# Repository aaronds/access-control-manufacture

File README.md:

# Access Control Manufacture

CAD / CAM assets for manufacturing access control boxes (aka "bleepy boxes").

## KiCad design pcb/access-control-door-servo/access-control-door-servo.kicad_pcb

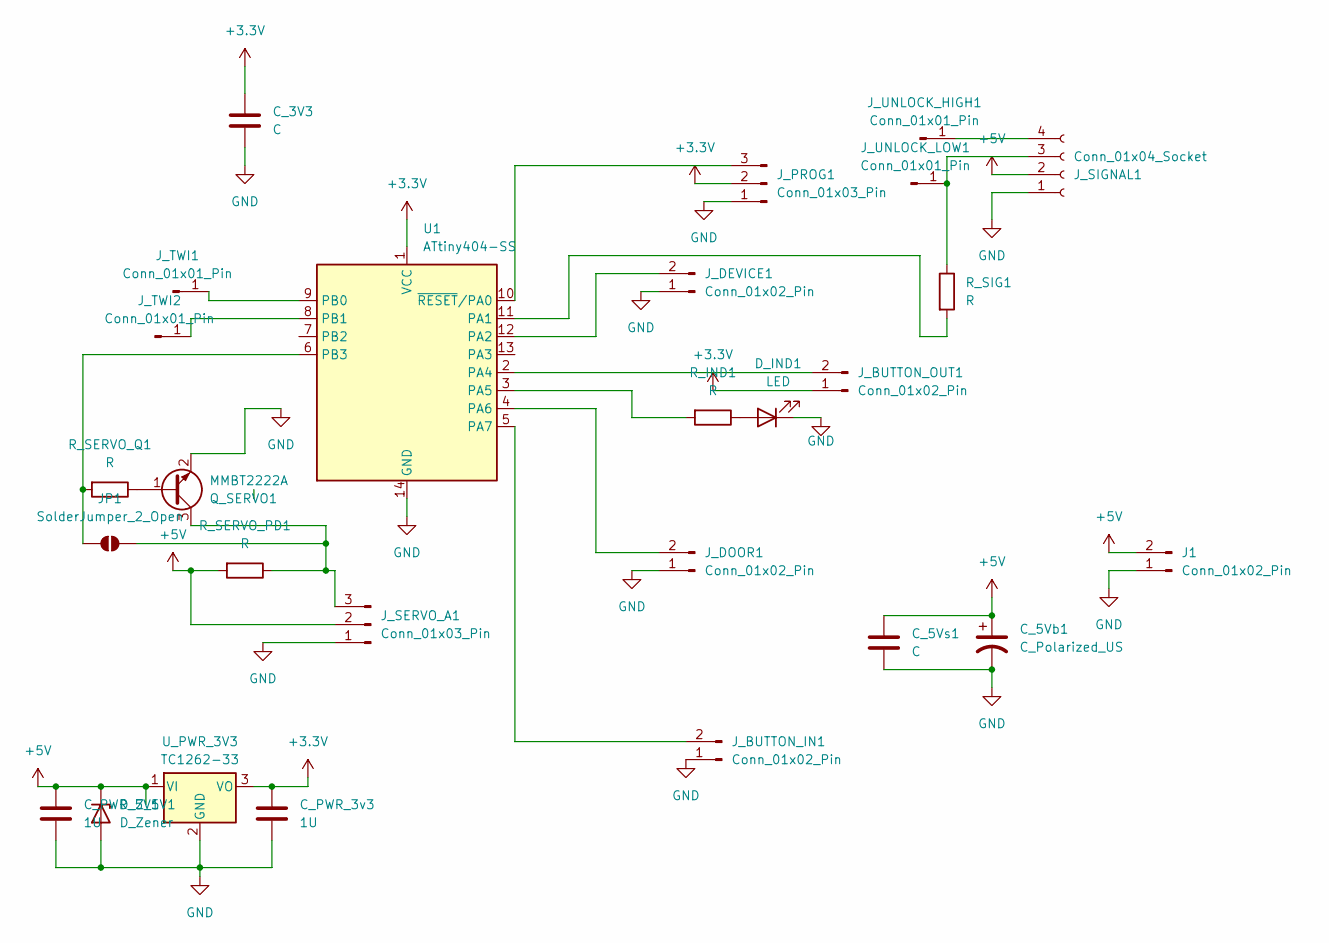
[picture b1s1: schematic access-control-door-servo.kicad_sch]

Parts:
C_3V3, C_5Vs1: C; C_1206_3216Metric
C_5Vb1: C_Polarized_US; CP_Radial_D5.0mm_P2.50mm
C_PWR_3v3, C_PWR_5V1: 1U; C_1206_3216Metric_Pad1.33x1.80mm_HandSolder
D_IND1: LED; LED_D10.0mm
D_Z_5V1: D_Zener; D_1206_3216Metric_Pad1.42x1.75mm_HandSolder
J1: Conn_01x02_Pin; JST_XH_B2B-XH-A_1x02_P2.50mm_Vertical
JP1: SolderJumper_2_Open; SolderJumper-2_P1.3mm_Open_TrianglePad1.0x1.5mm
J_BUTTON_IN1: Conn_01x02_Pin; PinSocket_1x02_P2.54mm_Vertical
J_BUTTON_OUT1: Conn_01x02_Pin; PinSocket_1x02_P2.54mm_Vertical
J_DEVICE1: Conn_01x02_Pin; PinHeader_1x02_P2.54mm_Vertical
J_DOOR1: Conn_01x02_Pin; PinHeader_1x02_P2.54mm_Vertical
J_PROG1: Conn_01x03_Pin; PinHeader_1x03_P2.54mm_Vertical
J_SERVO_A1: Conn_01x03_Pin; PinHeader_1x03_P2.54mm_Vertical
J_SIGNAL1: Conn_01x04_Socket; JST_XH_B4B-XH-A_1x04_P2.50mm_Vertical
J_TWI1, J_TWI2: Conn_01x01_Pin; SolderWirePad_1x01_SMD_1x2mm
J_UNLOCK_HIGH1: Conn_01x01_Pin; SolderWirePad_1x01_SMD_1x2mm
J_UNLOCK_LOW1: Conn_01x01_Pin; SolderWirePad_1x01_SMD_1x2mm
Q_SERVO1: MMBT2222A; SOT-23W_Handsoldering
R_IND1: R; R_1206_3216Metric
R_SERVO_PD1: R; R_1206_3216Metric
R_SERVO_Q1: R; R_1206_3216Metric
R_SIG1: R; R_1206_3216Metric
U1: ATtiny404-SS; SOIC-14_3.9x8.7mm_P1.27mm
U_PWR_3V3: TC1262-33; SOT-223-3_TabPin2

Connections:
+3.3V: C_3V3.1, C_PWR_3v3.1, J_BUTTON_OUT1.1, J_PROG1.2, U1.1 (VCC), U_PWR_3V3.3 (VO)
+5V: C_5Vb1.1, C_5Vs1.1, C_PWR_5V1.1, D_Z_5V1.1 (K), J1.2, J_SERVO_A1.2, J_SIGNAL1.2, R_SERVO_PD1.2, U_PWR_3V3.1 (VI)
GND: C_3V3.2, C_5Vb1.2, C_5Vs1.2, C_PWR_3v3.2, C_PWR_5V1.2, D_IND1.1 (K), D_Z_5V1.2 (A), J1.1, J_BUTTON_IN1.1, J_DEVICE1.1, J_DOOR1.1, J_PROG1.1, J_SERVO_A1.1, J_SIGNAL1.1, Q_SERVO1.2 (E), U1.14 (GND), U_PWR_3V3.2 (GND)
unnamed: D_IND1.2 (A), R_IND1.1
unnamed: JP1.1 (A), R_SERVO_Q1.2, U1.6 (PB3)
unnamed: JP1.2 (B), J_SERVO_A1.3, Q_SERVO1.3 (C), R_SERVO_PD1.1
unnamed: J_BUTTON_IN1.2, U1.5 (PA7)
unnamed: J_BUTTON_OUT1.2, U1.2 (PA4)
unnamed: J_DEVICE1.2, U1.12 (PA2)
unnamed: J_DOOR1.2, U1.4 (PA6)
unnamed: J_PROG1.3, U1.10 (~RESET/PA0)
unnamed: J_SIGNAL1.3, J_UNLOCK_LOW1.1, R_SIG1.1
unnamed: J_SIGNAL1.4, J_UNLOCK_HIGH1.1
unnamed: J_TWI1.1, U1.9 (PB0)
unnamed: J_TWI2.1, U1.8 (PB1)
unnamed: Q_SERVO1.1 (B), R_SERVO_Q1.1
unnamed: R_SIG1.2, U1.11 (PA1)
unnamed: R_IND1.2, U1.3 (PA5)

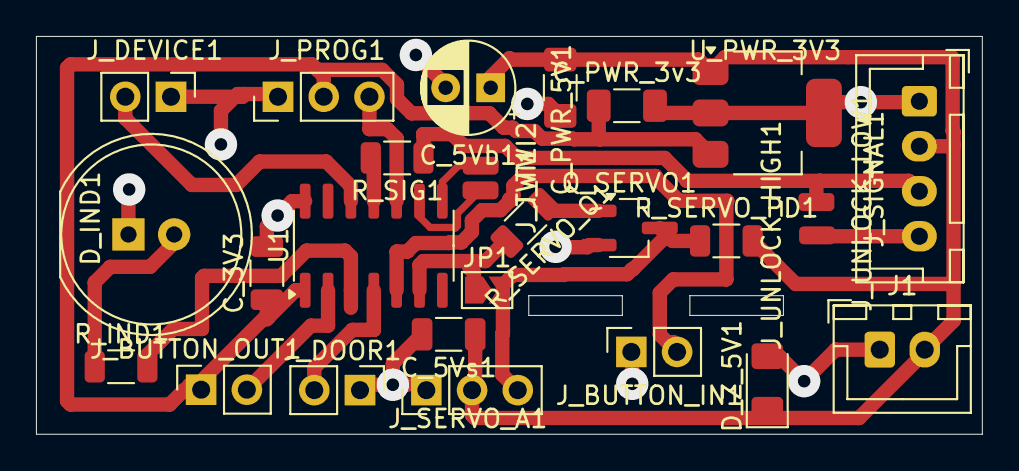
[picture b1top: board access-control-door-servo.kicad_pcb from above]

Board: 2 copper layers, 52.5 x 22.1 mm, 27 parts (0 on the bottom side), 18 nets.

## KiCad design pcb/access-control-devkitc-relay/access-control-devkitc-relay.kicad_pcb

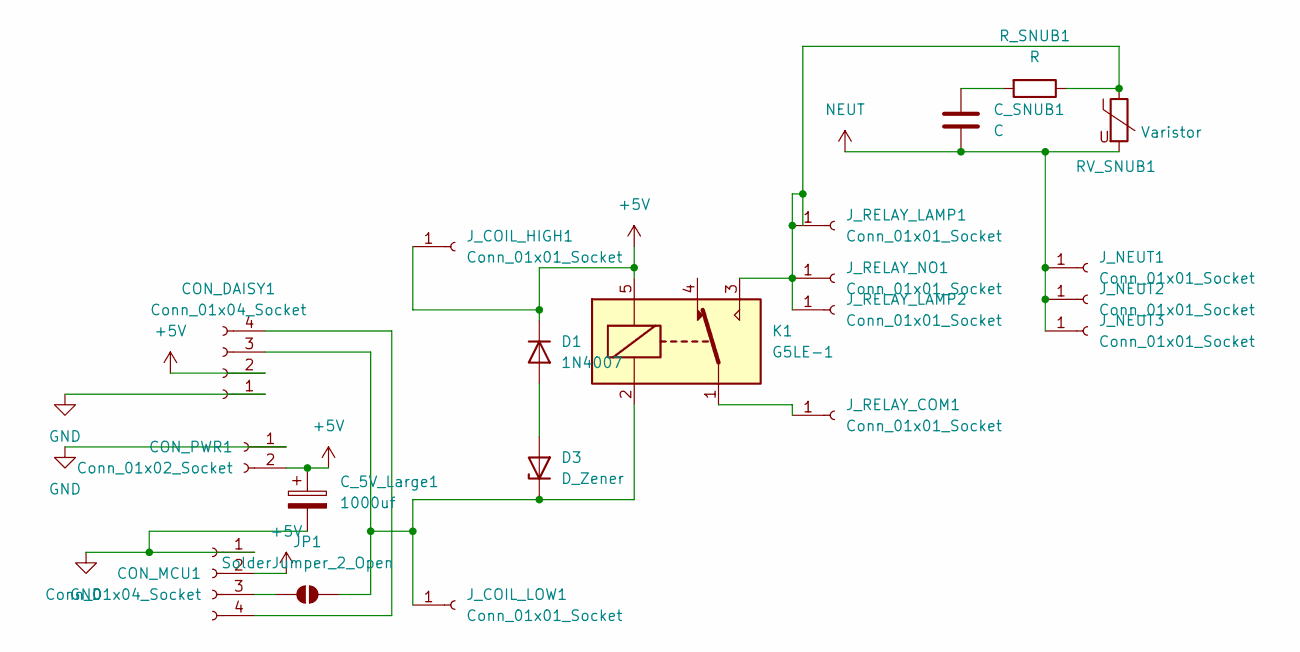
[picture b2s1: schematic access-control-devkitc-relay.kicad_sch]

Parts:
CON_DAISY1: Conn_01x04_Socket; JST_XA_B04B-XASK-1_1x04_P2.50mm_Vertical
CON_MCU1: Conn_01x04_Socket; PinHeader_1x04_P2.54mm_Vertical
CON_PWR1: Conn_01x02_Socket; JST_XH_B2B-XH-A_1x02_P2.50mm_Vertical
C_5V_Large1: 1000uf; CP_Radial_D8.0mm_P5.00mm
C_SNUB1: C; CP_Axial_L10.0mm_D6.0mm_P15.00mm_Horizontal
D1: 1N4007; D_DO-41_SOD81_P10.16mm_Horizontal
D3: D_Zener; D_DO-41_SOD81_P10.16mm_Horizontal
JP1: SolderJumper_2_Open; SolderJumper-2_P1.3mm_Open_TrianglePad1.0x1.5mm
J_COIL_HIGH1: Conn_01x01_Socket; SolderWire-1sqmm_1x01_D1.4mm_OD2.7mm
J_COIL_LOW1: Conn_01x01_Socket; SolderWire-1sqmm_1x01_D1.4mm_OD2.7mm
J_NEUT1, J_NEUT2, J_NEUT3: Conn_01x01_Socket; SolderWire-2.5sqmm_1x01_D2.4mm_OD4.4mm
J_RELAY_COM1: Conn_01x01_Socket; SolderWire-2.5sqmm_1x01_D2.4mm_OD4.4mm
J_RELAY_LAMP1, J_RELAY_LAMP2: Conn_01x01_Socket; SolderWire-2.5sqmm_1x01_D2.4mm_OD4.4mm
J_RELAY_NO1: Conn_01x01_Socket; SolderWire-2.5sqmm_1x01_D2.4mm_OD4.4mm
K1: G5LE-1; Relay_SPDT_Omron-G5LE-1
RV_SNUB1: Varistor; RV_Disc_D12mm_W3.9mm_P7.5mm
R_SNUB1: R; R_Axial_DIN0617_L17.0mm_D6.0mm_P20.32mm_Horizontal

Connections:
+5V: CON_DAISY1.2, CON_MCU1.2, CON_PWR1.2, C_5V_Large1.1, D1.1 (K), J_COIL_HIGH1.1, K1.5
GND: CON_DAISY1.1, CON_MCU1.1, CON_PWR1.1, C_5V_Large1.2
NEUT: C_SNUB1.2, J_NEUT1.1, J_NEUT2.1, J_NEUT3.1, RV_SNUB1.2
unnamed: CON_DAISY1.3, D3.1 (K), JP1.2 (B), J_COIL_LOW1.1, K1.2
unnamed: CON_DAISY1.4, CON_MCU1.4
unnamed: CON_MCU1.3, JP1.1 (A)
unnamed: C_SNUB1.1, R_SNUB1.2
unnamed: D1.2 (A), D3.2 (A)
unnamed: J_RELAY_COM1.1, K1.1
unnamed: J_RELAY_LAMP1.1, J_RELAY_LAMP2.1, J_RELAY_NO1.1, K1.3, RV_SNUB1.1, R_SNUB1.1

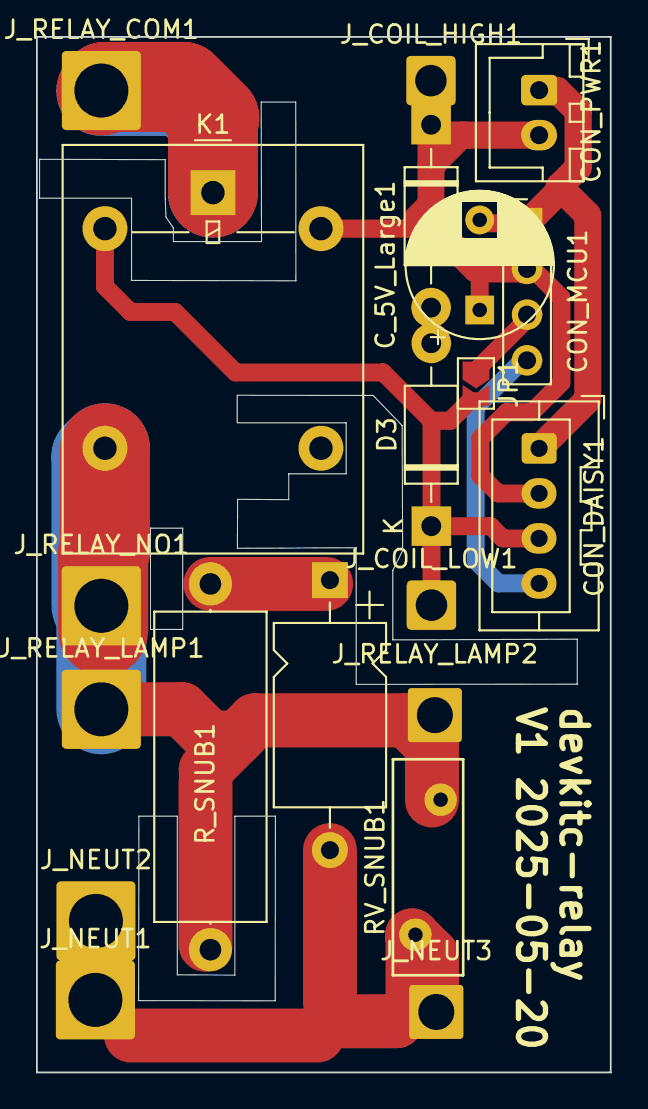
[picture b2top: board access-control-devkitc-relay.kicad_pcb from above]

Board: 2 copper layers, 31.9 x 57.5 mm, 20 parts (0 on the bottom side), 10 nets.

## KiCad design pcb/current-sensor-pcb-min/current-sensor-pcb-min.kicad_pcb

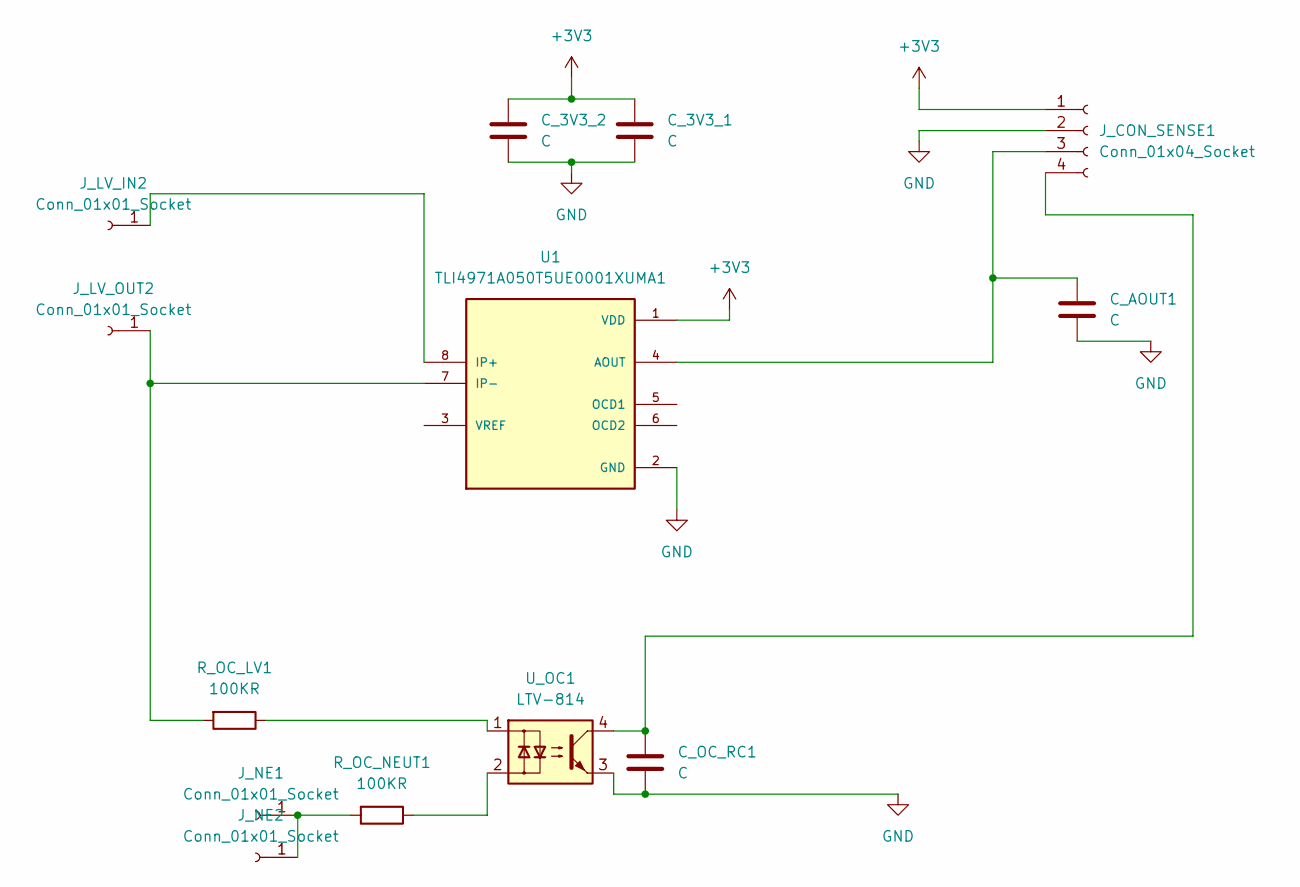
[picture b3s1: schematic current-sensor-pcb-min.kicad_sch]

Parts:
C_3V3_1, C_3V3_2: C; C_Disc_D3.8mm_W2.6mm_P2.50mm
C_AOUT1: C; C_Disc_D3.8mm_W2.6mm_P2.50mm
C_OC_RC1: C; C_Disc_D5.0mm_W2.5mm_P5.00mm
J_CON_SENSE1: Conn_01x04_Socket; PinHeader_1x04_P2.54mm_Vertical
J_LV_IN2: Conn_01x01_Socket; SolderWirePad_1x01_SMD_5x10mm
J_LV_OUT2: Conn_01x01_Socket; SolderWirePad_1x01_SMD_5x10mm
J_NE1, J_NE2: Conn_01x01_Socket; SolderWire-2.5sqmm_1x01_D2.4mm_OD3.6mm
R_OC_LV1: 100KR; R_Axial_DIN0617_L17.0mm_D6.0mm_P20.32mm_Horizontal
R_OC_NEUT1: 100KR; R_Axial_DIN0617_L17.0mm_D6.0mm_P20.32mm_Horizontal
U1: TLI4971A050T5UE0001XUMA1; IC_TLI4971A050T5UE0001XUMA1; PARTREV 1.20
U_OC1: LTV-814; DIP-4_W7.62mm

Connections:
+3V3: C_3V3_1.1, C_3V3_2.1, J_CON_SENSE1.1, U1.1 (VDD)
GND: C_3V3_1.2, C_3V3_2.2, C_AOUT1.2, C_OC_RC1.2, J_CON_SENSE1.2, U1.2 (GND), U_OC1.3
unnamed: C_AOUT1.1, J_CON_SENSE1.3, U1.4 (AOUT)
unnamed: C_OC_RC1.1, J_CON_SENSE1.4, U_OC1.4
unnamed: J_LV_IN2.1, U1.8 (IP+)
unnamed: J_LV_OUT2.1, R_OC_LV1.2, U1.7 (IP-)
unnamed: J_NE1.1, J_NE2.1, R_OC_NEUT1.2
unnamed: R_OC_LV1.1, U_OC1.1
unnamed: R_OC_NEUT1.1, U_OC1.2

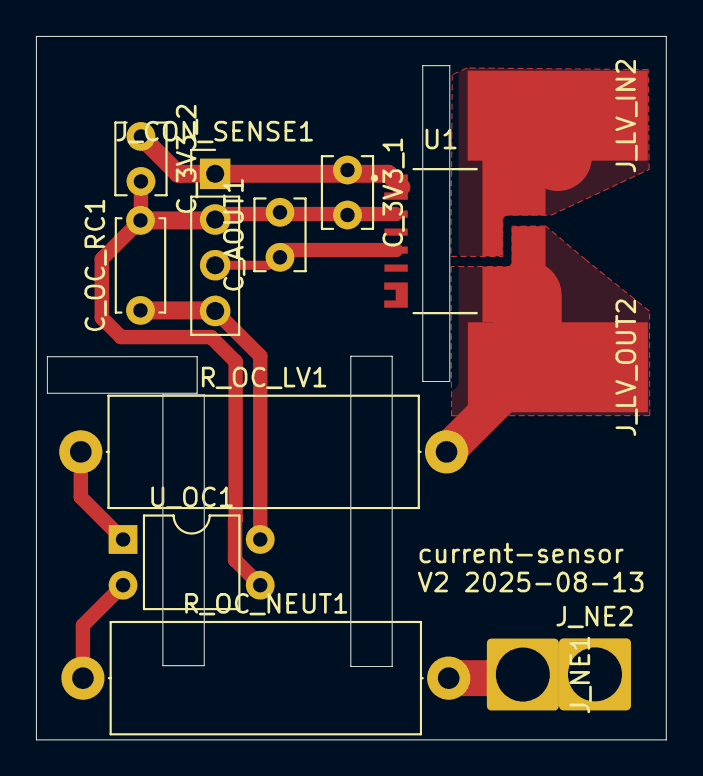
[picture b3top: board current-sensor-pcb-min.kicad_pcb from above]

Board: 2 copper layers, 35.0 x 39.1 mm, 13 parts (0 on the bottom side), 9 nets.

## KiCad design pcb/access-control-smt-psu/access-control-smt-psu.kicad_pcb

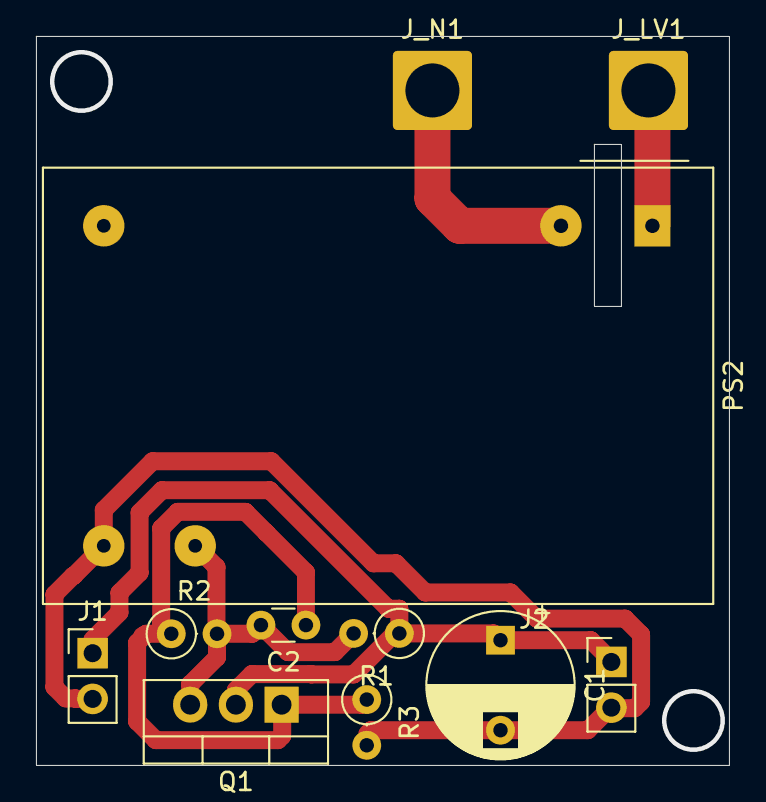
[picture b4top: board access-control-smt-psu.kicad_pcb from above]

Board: 2 copper layers, 38.5 x 40.5 mm, 11 parts (0 on the bottom side), 5 nets.

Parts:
C1: C_Polarized; CP_Radial_D8.0mm_P5.00mm
C2: C1u; C_Disc_D3.0mm_W1.6mm_P2.50mm
J1, J2: Conn_01x02_Socket; PinHeader_1x02_P2.54mm_Vertical
J_LV1: Conn_01x01_Pin; SolderWire-2.5sqmm_1x01_D2.4mm_OD4.4mm
J_N1: Conn_01x01_Pin; SolderWire-2.5sqmm_1x01_D2.4mm_OD4.4mm
PS2: IRM-03-5; Converter_ACDC_MeanWell_IRM-03-xx_THT
Q1: IRF9540N; TO-220-3_Vertical
R1: R1; R_Axial_DIN0207_L6.3mm_D2.5mm_P2.54mm_Vertical
R2: R150k; R_Axial_DIN0207_L6.3mm_D2.5mm_P2.54mm_Vertical
R3: R8.6k; R_Axial_DIN0207_L6.3mm_D2.5mm_P2.54mm_Vertical

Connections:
unnamed: C1.1, J1.1, J2.1, Q1.2 (D), R1.1
unnamed: J_LV1.1, PS2.1 (AC/L)
unnamed: J_N1.1, PS2.3 (AC/N)
unnamed: C2.2, PS2.16 (+Vo), Q1.3 (S), R1.2, R2.2
unnamed: C2.1, Q1.1 (G), R2.1, R3.1

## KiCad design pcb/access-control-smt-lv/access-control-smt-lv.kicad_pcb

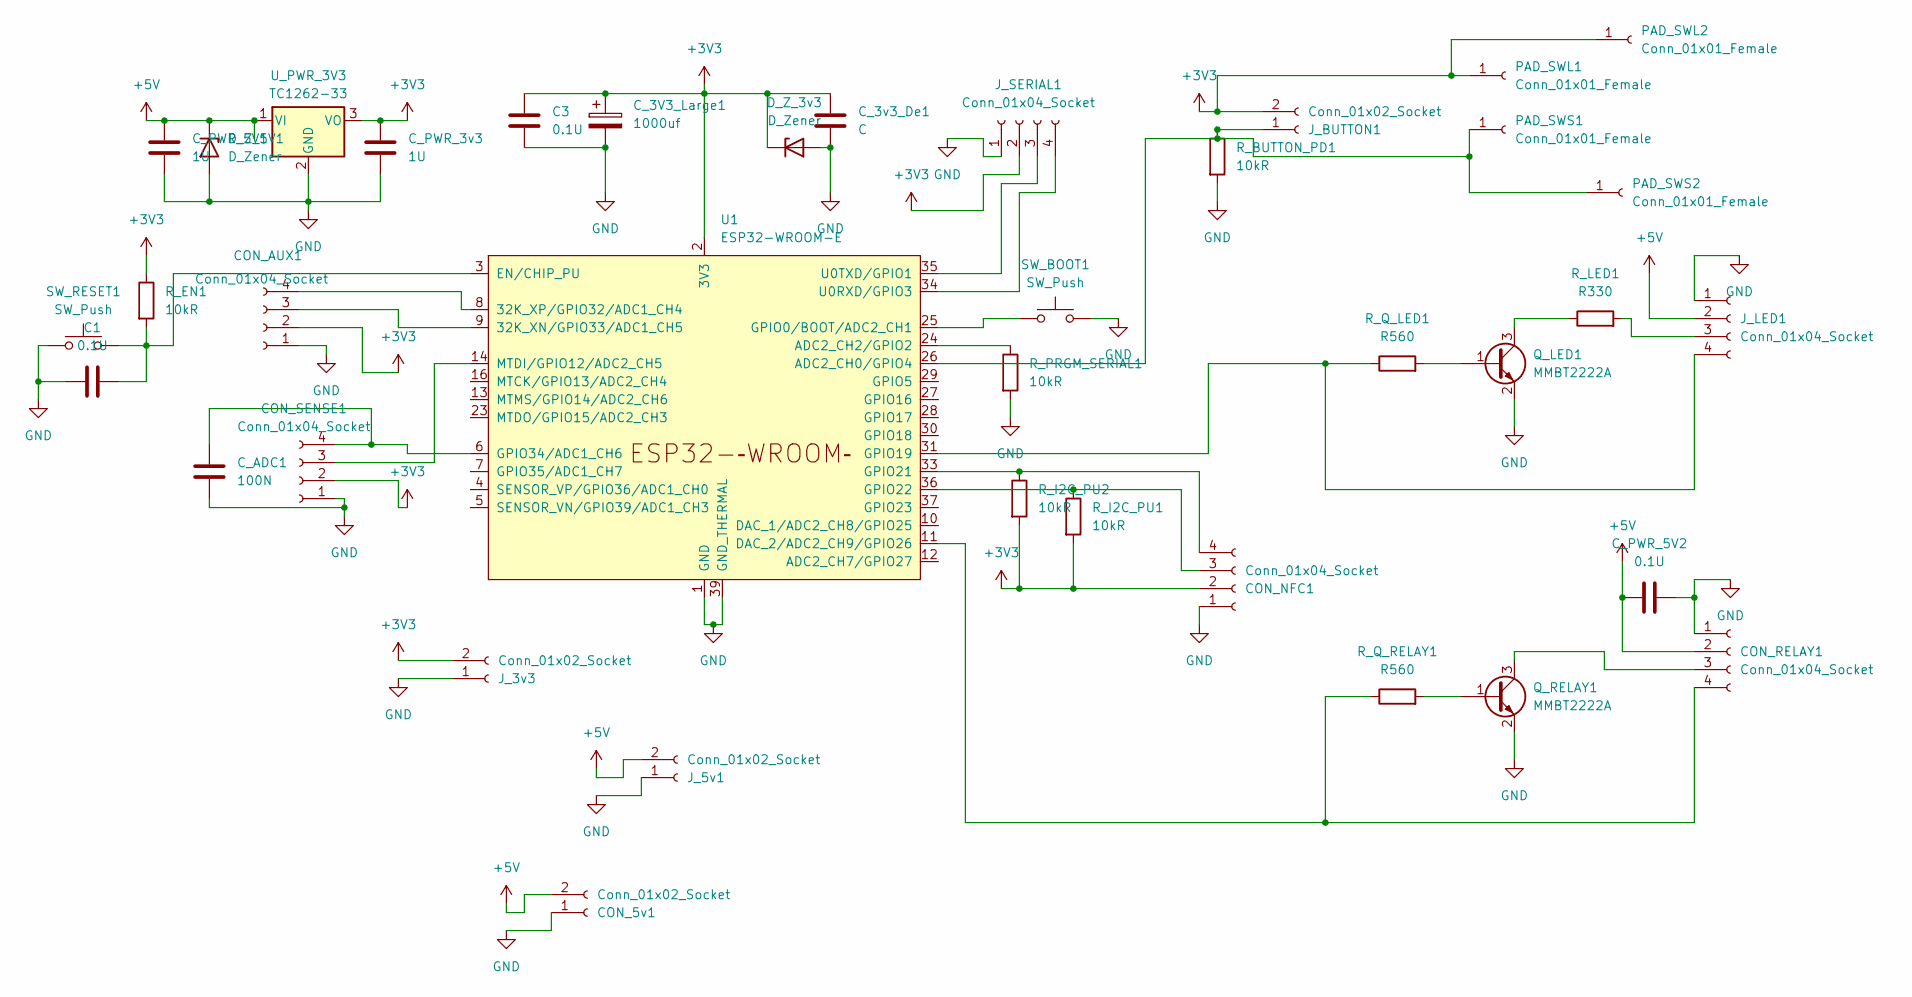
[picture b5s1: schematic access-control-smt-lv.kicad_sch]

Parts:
C1, C3: 0.1U; C_1206_3216Metric_Pad1.33x1.80mm_HandSolder
CON_5v1: Conn_01x02_Socket; JST_XH_B2B-XH-A_1x02_P2.50mm_Vertical
CON_AUX1: Conn_01x04_Socket; PinHeader_1x04_P2.54mm_Vertical
CON_NFC1: Conn_01x04_Socket; JST_XH_B4B-XH-A_1x04_P2.50mm_Vertical
CON_RELAY1: Conn_01x04_Socket; JST_XH_B4B-XH-A_1x04_P2.50mm_Vertical
CON_SENSE1: Conn_01x04_Socket; JST_XH_B4B-XH-A_1x04_P2.50mm_Vertical
C_3V3_Large1: 1000uf; CP_Radial_D8.0mm_P5.00mm
C_3v3_De1: C; C_Disc_D3.4mm_W2.1mm_P2.50mm
C_ADC1: 100N; C_1206_3216Metric_Pad1.33x1.80mm_HandSolder
C_PWR_3v3, C_PWR_5V1: 1U; C_1206_3216Metric_Pad1.33x1.80mm_HandSolder
C_PWR_5V2: 0.1U; C_1206_3216Metric_Pad1.33x1.80mm_HandSolder
D_Z_3v3: D_Zener; D_0805_2012Metric_Pad1.15x1.40mm_HandSolder
D_Z_5V1: D_Zener; D_1206_3216Metric_Pad1.42x1.75mm_HandSolder
J_3v3, J_5v1: Conn_01x02_Socket; PinHeader_1x02_P2.54mm_Vertical
J_BUTTON1: Conn_01x02_Socket; PinHeader_1x02_P2.54mm_Vertical
J_LED1: Conn_01x04_Socket; PinSocket_1x04_P2.54mm_Vertical
J_SERIAL1: Conn_01x04_Socket; JST_XH_B4B-XH-A_1x04_P2.50mm_Vertical
PAD_SWL1, PAD_SWL2: Conn_01x01_Female; SolderWirePad_1x01_SMD_1x2mm
PAD_SWS1, PAD_SWS2: Conn_01x01_Female; SolderWirePad_1x01_SMD_1x2mm
Q_LED1: MMBT2222A; SOT-23W_Handsoldering
Q_RELAY1: MMBT2222A; SOT-23W_Handsoldering
R_BUTTON_PD1: 10kR; R_1206_3216Metric_Pad1.30x1.75mm_HandSolder
R_EN1: 10kR; R_1206_3216Metric_Pad1.30x1.75mm_HandSolder
R_I2C_PU1, R_I2C_PU2: 10kR; R_1206_3216Metric_Pad1.30x1.75mm_HandSolder
R_LED1: R330; R_1206_3216Metric_Pad1.30x1.75mm_HandSolder
R_PRGM_SERIAL1: 10kR; R_1206_3216Metric_Pad1.30x1.75mm_HandSolder
R_Q_LED1: R560; R_1206_3216Metric_Pad1.30x1.75mm_HandSolder
R_Q_RELAY1: R560; R_1206_3216Metric_Pad1.30x1.75mm_HandSolder
SW_BOOT1: SW_Push; SW_SPST_B3S-1000
SW_RESET1: SW_Push; SW_SPST_B3S-1000
U1: ESP32-WROOM-E; ESP32-WROOM-32E
U_PWR_3V3: TC1262-33; SOT-223-3_TabPin2

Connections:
+3V3: C3.1, CON_AUX1.2, CON_NFC1.2, CON_SENSE1.2, C_3V3_Large1.1, C_3v3_De1.1, C_PWR_3v3.1, D_Z_3v3.1 (K), J_3v3.2, J_BUTTON1.2, J_SERIAL1.2, PAD_SWL1.1, PAD_SWL2.1, R_EN1.1, R_I2C_PU1.2, R_I2C_PU2.2, U1.2 (3V3), U_PWR_3V3.3 (VO)
+5V: CON_5v1.2, CON_RELAY1.2, C_PWR_5V1.1, C_PWR_5V2.1, D_Z_5V1.1 (K), J_5v1.2, J_LED1.2, U_PWR_3V3.1 (VI)
GND: C1.2, C3.2, CON_5v1.1, CON_AUX1.1, CON_NFC1.1, CON_RELAY1.1, CON_SENSE1.1, C_3V3_Large1.2, C_3v3_De1.2, C_ADC1.2, C_PWR_3v3.2, C_PWR_5V1.2, C_PWR_5V2.2, D_Z_3v3.2 (A), D_Z_5V1.2 (A), J_3v3.1, J_5v1.1, J_LED1.1, J_SERIAL1.1, Q_LED1.2 (E), Q_RELAY1.2 (E), R_BUTTON_PD1.2, R_PRGM_SERIAL1.2, SW_BOOT1.2, SW_RESET1.1, U1.1 (GND), U1.15 (GND), U1.38 (GND), U1.39 (GND_THERMAL), U_PWR_3V3.2 (GND)
unnamed: CON_AUX1.3, U1.9 (32K_XN/GPIO33/ADC1_CH5)
unnamed: CON_AUX1.4, U1.8 (32K_XP/GPIO32/ADC1_CH4)
unnamed: CON_NFC1.3, R_I2C_PU1.1, U1.36 (GPIO22)
unnamed: CON_NFC1.4, R_I2C_PU2.1, U1.33 (GPIO21)
unnamed: CON_RELAY1.3, Q_RELAY1.3 (C)
unnamed: CON_RELAY1.4, R_Q_RELAY1.1, U1.11 (DAC_2/ADC2_CH9/GPIO26)
unnamed: CON_SENSE1.3, U1.14 (MTDI/GPIO12/ADC2_CH5)
unnamed: CON_SENSE1.4, C_ADC1.1, U1.6 (GPIO34/ADC1_CH6)
unnamed: J_BUTTON1.1, PAD_SWS1.1, PAD_SWS2.1, R_BUTTON_PD1.1, U1.26 (ADC2_CH0/GPIO4)
unnamed: J_LED1.3, R_LED1.2
unnamed: J_LED1.4, R_Q_LED1.1, U1.31 (GPIO19)
unnamed: J_SERIAL1.3, U1.35 (U0TXD/GPIO1)
unnamed: J_SERIAL1.4, U1.34 (U0RXD/GPIO3)
unnamed: Q_LED1.1 (B), R_Q_LED1.2
unnamed: Q_LED1.3 (C), R_LED1.1
unnamed: Q_RELAY1.1 (B), R_Q_RELAY1.2
unnamed: R_PRGM_SERIAL1.1, U1.24 (ADC2_CH2/GPIO2)
unnamed: C1.1, R_EN1.2, SW_RESET1.2, U1.3 (EN/CHIP_PU)
unnamed: SW_BOOT1.1, U1.25 (GPIO0/BOOT/ADC2_CH1)

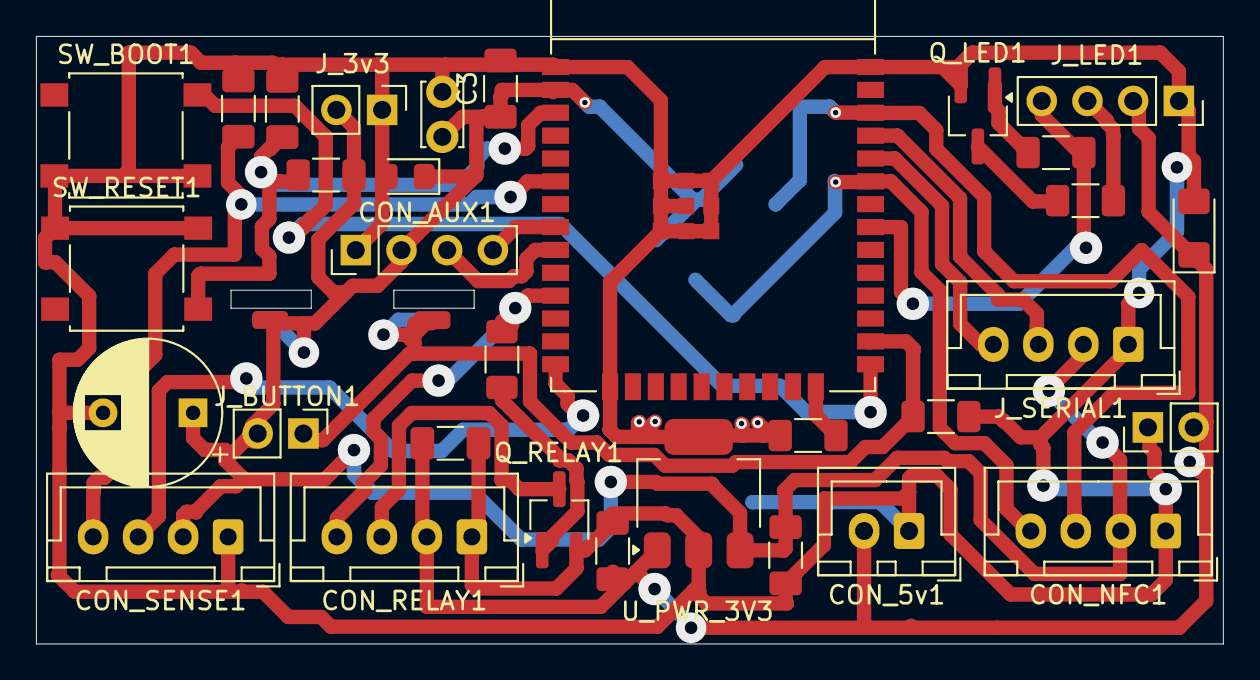
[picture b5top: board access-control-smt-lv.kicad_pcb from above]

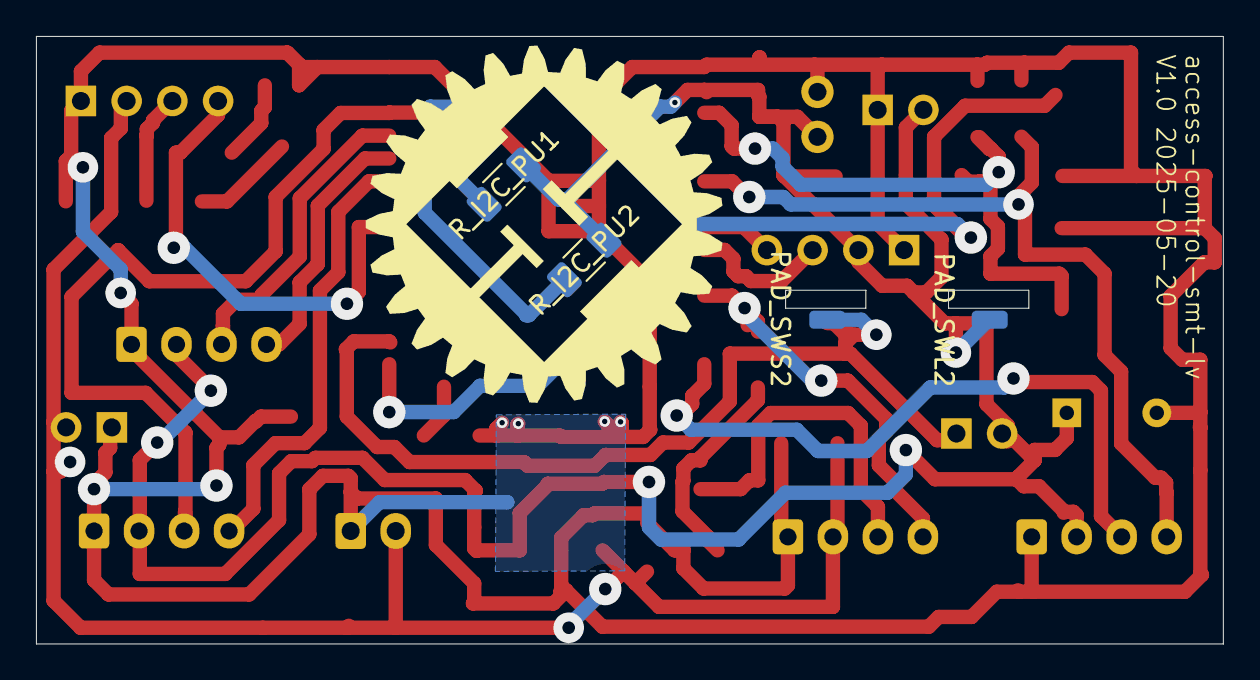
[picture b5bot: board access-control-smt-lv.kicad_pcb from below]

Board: 2 copper layers, 65.9 x 33.8 mm, 38 parts (4 on the bottom side), 22 nets.

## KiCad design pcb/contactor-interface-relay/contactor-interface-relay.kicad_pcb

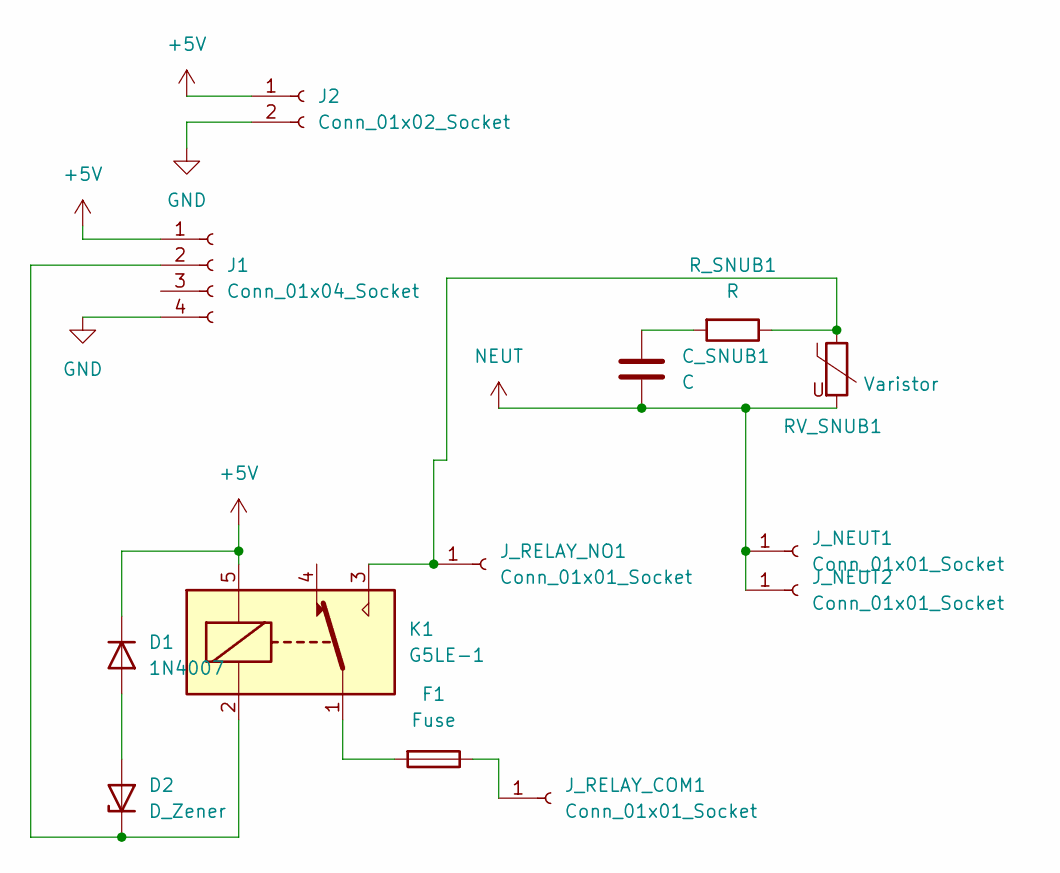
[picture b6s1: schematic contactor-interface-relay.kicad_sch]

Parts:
C_SNUB1: C; CP_Axial_L10.0mm_D6.0mm_P15.00mm_Horizontal
D1: 1N4007; D_DO-41_SOD81_P10.16mm_Horizontal
D2: D_Zener; D_DO-41_SOD81_P10.16mm_Horizontal
F1: Fuse; Fuse_Littelfuse_395Series
J1: Conn_01x04_Socket; PinHeader_1x04_P2.54mm_Vertical
J2: Conn_01x02_Socket; PinHeader_1x02_P2.54mm_Vertical
J_NEUT1, J_NEUT2: Conn_01x01_Socket; SolderWire-2.5sqmm_1x01_D2.4mm_OD4.4mm
J_RELAY_COM1: Conn_01x01_Socket; SolderWire-2.5sqmm_1x01_D2.4mm_OD4.4mm
J_RELAY_NO1: Conn_01x01_Socket; SolderWire-2.5sqmm_1x01_D2.4mm_OD4.4mm
K1: G5LE-1; Relay_SPDT_Omron-G5LE-1
RV_SNUB1: Varistor; RV_Disc_D12mm_W3.9mm_P7.5mm
R_SNUB1: R; R_Axial_DIN0617_L17.0mm_D6.0mm_P20.32mm_Horizontal

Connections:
+5V: D1.1 (K), J1.1, J2.1, K1.5
GND: J1.4, J2.2
NEUT: C_SNUB1.2, J_NEUT1.1, J_NEUT2.1, RV_SNUB1.2
unnamed: C_SNUB1.1, R_SNUB1.2
unnamed: D1.2 (A), D2.2 (A)
unnamed: D2.1 (K), J1.2, K1.2
unnamed: F1.2, K1.1
unnamed: F1.1, J_RELAY_COM1.1
unnamed: J_RELAY_NO1.1, K1.3, RV_SNUB1.1, R_SNUB1.1

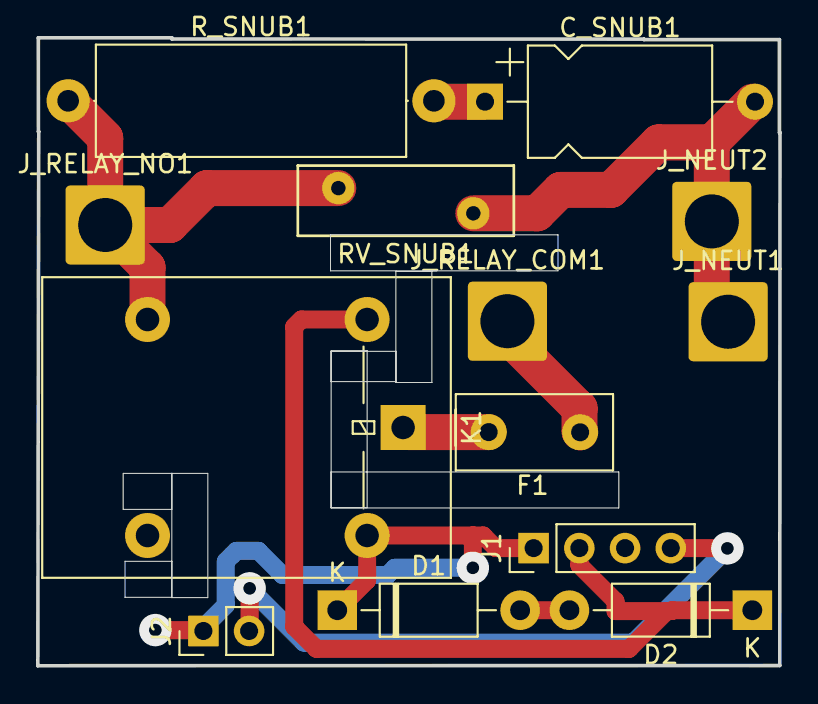
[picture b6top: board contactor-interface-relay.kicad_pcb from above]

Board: 2 copper layers, 41.2 x 34.9 mm, 13 parts (0 on the bottom side), 9 nets.

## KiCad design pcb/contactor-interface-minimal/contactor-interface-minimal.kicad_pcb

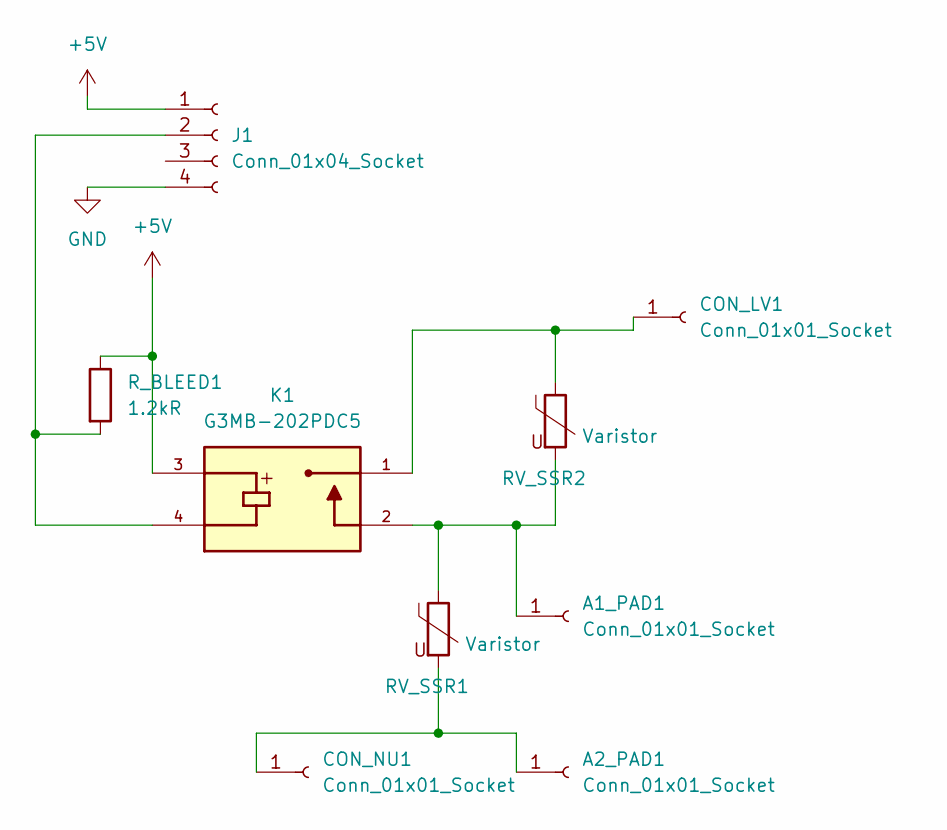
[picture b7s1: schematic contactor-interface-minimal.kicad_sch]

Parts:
A1_PAD1, A2_PAD1: Conn_01x01_Socket; SolderWire-2.5sqmm_1x01_D2.4mm_OD3.6mm
CON_LV1: Conn_01x01_Socket; SolderWire-2.5sqmm_1x01_D2.4mm_OD3.6mm
CON_NU1: Conn_01x01_Socket; SolderWire-2.5sqmm_1x01_D2.4mm_OD3.6mm
J1: Conn_01x04_Socket; PinHeader_1x04_P2.54mm_Vertical
K1: G3MB-202PDC5; RELAY_G3MB-202PDC5; PARTREV J091-E1-1A
RV_SSR1, RV_SSR2: Varistor; RV_Disc_D12mm_W3.9mm_P7.5mm
R_BLEED1: 1.2kR; R_Axial_DIN0207_L6.3mm_D2.5mm_P10.16mm_Horizontal

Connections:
+5V: J1.1, K1.3, R_BLEED1.1
GND: J1.4
unnamed: A1_PAD1.1, K1.2, RV_SSR1.1, RV_SSR2.2
unnamed: A2_PAD1.1, CON_NU1.1, RV_SSR1.2
unnamed: CON_LV1.1, K1.1, RV_SSR2.1
unnamed: J1.2, K1.4, R_BLEED1.2

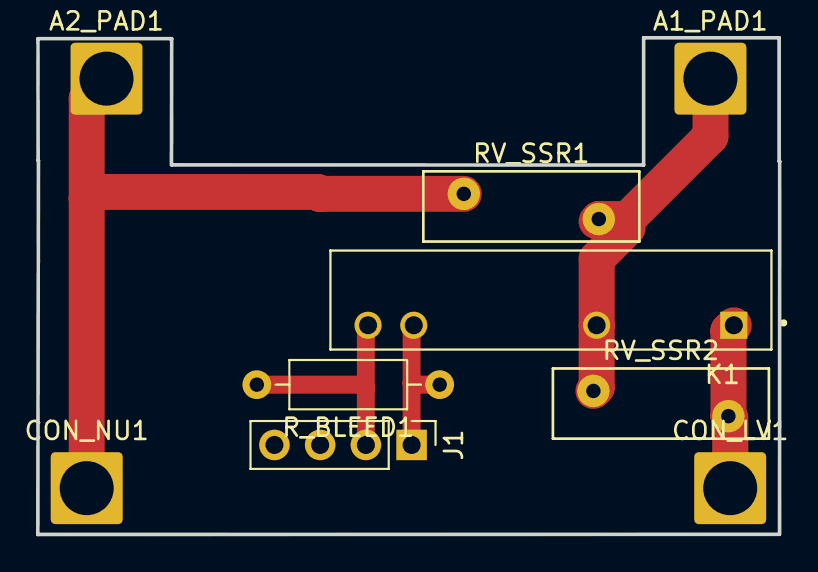
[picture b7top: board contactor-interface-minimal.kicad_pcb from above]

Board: 2 copper layers, 41.2 x 27.6 mm, 9 parts (0 on the bottom side), 5 nets.

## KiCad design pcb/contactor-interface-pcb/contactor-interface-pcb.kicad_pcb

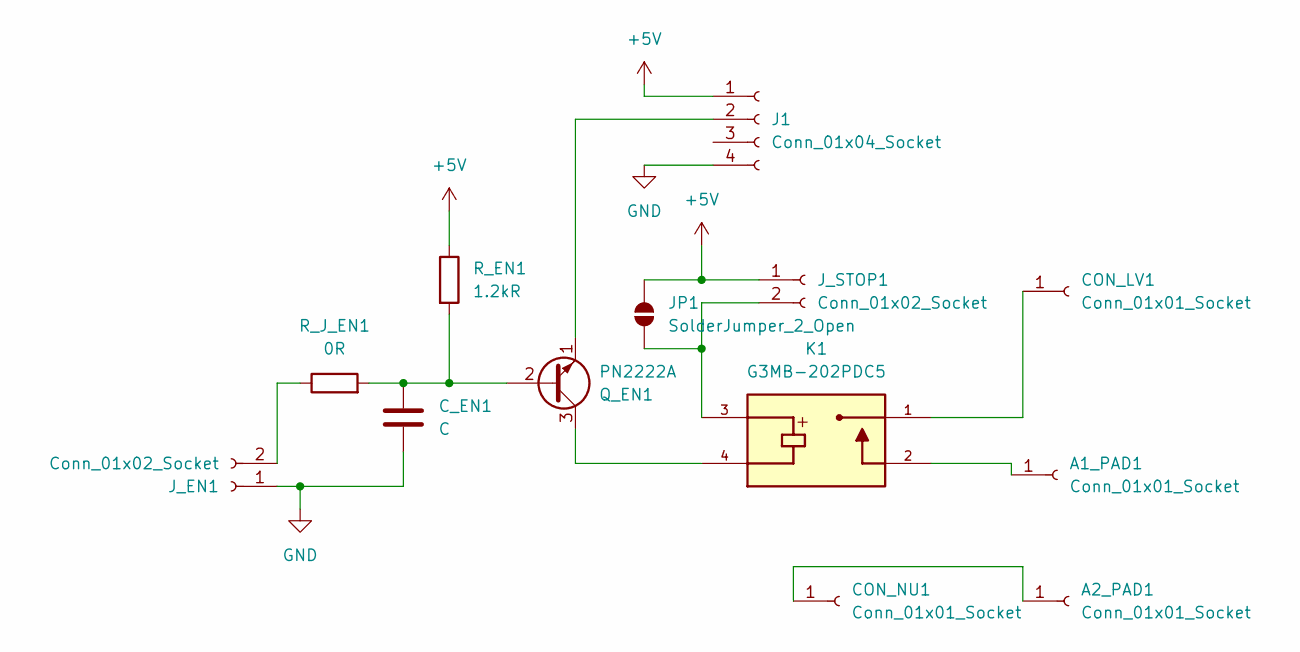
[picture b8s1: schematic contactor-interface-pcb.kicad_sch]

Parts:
A1_PAD1, A2_PAD1: Conn_01x01_Socket; SolderWire-2.5sqmm_1x01_D2.4mm_OD3.6mm
CON_LV1: Conn_01x01_Socket; SolderWire-2.5sqmm_1x01_D2.4mm_OD3.6mm
CON_NU1: Conn_01x01_Socket; SolderWire-2.5sqmm_1x01_D2.4mm_OD3.6mm
C_EN1: C; C_Disc_D4.3mm_W1.9mm_P5.00mm
J1: Conn_01x04_Socket; PinHeader_1x04_P2.54mm_Vertical
JP1: SolderJumper_2_Open; SolderJumper-2_P1.3mm_Open_TrianglePad1.0x1.5mm
J_EN1: Conn_01x02_Socket; PinHeader_1x02_P2.54mm_Vertical
J_STOP1: Conn_01x02_Socket; PinHeader_1x02_P2.54mm_Vertical
K1: G3MB-202PDC5; RELAY_G3MB-202PDC5; PARTREV J091-E1-1A
Q_EN1: PN2222A; TO-92_HandSolder
R_EN1: 1.2kR; R_Axial_DIN0207_L6.3mm_D2.5mm_P10.16mm_Horizontal
R_J_EN1: 0R; R_Axial_DIN0207_L6.3mm_D2.5mm_P10.16mm_Horizontal

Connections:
+5V: J1.1, JP1.1 (A), J_STOP1.1, R_EN1.1
GND: C_EN1.2, J1.4, J_EN1.1
unnamed: A1_PAD1.1, K1.2
unnamed: A2_PAD1.1, CON_NU1.1
unnamed: CON_LV1.1, K1.1
unnamed: J1.2, Q_EN1.1 (E)
unnamed: JP1.2 (B), J_STOP1.2, K1.3
unnamed: J_EN1.2, R_J_EN1.1
unnamed: C_EN1.1, Q_EN1.2 (B), R_EN1.2, R_J_EN1.2
unnamed: K1.4, Q_EN1.3 (C)

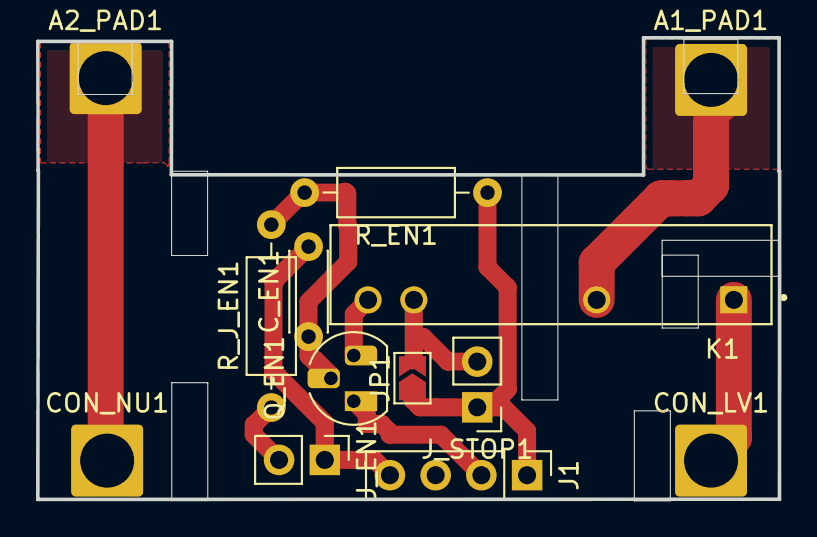
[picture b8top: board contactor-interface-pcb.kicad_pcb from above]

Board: 2 copper layers, 41.2 x 25.6 mm, 13 parts (0 on the bottom side), 10 nets.

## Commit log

2024-12-06 Inital commit milling files
2024-12-06 Pannel PCB Design
2024-12-06 Updating for origin issues
2024-12-07 Minor updates to component sizes
2024-12-08 Commit to transfer
2024-12-08 Adding cover
2024-12-08 First stab at a cover
2024-12-09 Updates and cover
2024-12-09 LED connector and cover to sit over
2024-12-10 Change LED handling
2024-12-22 Lamp connectors
2024-12-22 Lamp PCB, strip wire test and recut switch holes
2024-12-23 Wire strip work holding
2024-12-23 Updated with correct measurements and G43.* behaviour
2024-12-29 Updates after testing
2024-12-31 Strip wire subroutine, cover to cover lamp
2024-12-31 Adding solid wires spec
2025-01-11 Wire stripping
2025-01-12 Wire stripping fixtures
2025-01-13 One block wire holding
2025-01-15 Further refinement
2025-01-15 Strip the blue wires
2025-01-15 Update with wire corrections
2025-01-15 Correcting strip operations
2025-01-23 Adding minimum depth version
2025-01-25 Smaller pannel PCB
2025-01-27 A desk clamp and progress with minimal pannel
2025-02-12 Add values for refernce
2025-02-12 Refined access controll dev box
2025-02-14 Updates with AUX
2025-02-17 Further optimisation
2025-02-18 Split board into Low Voltage / Relay modules
2025-02-20 Containers for devkit
2025-02-26 Update with values
2025-02-26 NFC Container
2025-02-28 Updates for manufacturing
2025-03-02 Redability updates to schematic
2025-03-08 Contactor interface and current sensor (part only)
2025-03-09 Progress with current sensor
2025-03-14 Correcting box hole O words
2025-03-15 Progress with SMT controller and contactor variant
2025-03-15 Mostly done SMT controller
2025-03-16 NFC Clamp and progress with contactor interface
2025-03-17 Slight refactor of contator components to support more compact layout
2025-03-17 Update ignores
2025-03-21 Further optimisation of SMT version
2025-03-29 Current sensor progress
2025-04-23 Adding fuse for contactor coil
2025-04-27 Extra 5v / ground connections
2025-04-27 DIN Rail Clip profile from https://www.thingiverse.com/thing:5186799
    Originally from https://www.thingiverse.com/thing:101024
2025-04-27 Front plate to hold the NFC
2025-04-29 DIN mount for PSU
2025-05-02 SMT PCB Updates
2025-05-06 Fixes to relief, JST connectors for SMT board
2025-05-14 Relay and Current sensor enclosure
2025-05-17 Silkscreen updates with version, date and logo
2025-05-21 Final changes pre manufacture
2025-06-01 Option for 5v out on the other side
2025-07-01 Attempt to de-conflict the lamp from contactor interface
2025-07-01 And size changes
2025-07-01 Changes for proper PCB
2025-07-03 Minor fixes
2025-07-06 Updated with clearance for contactor
2025-07-21 Clearance fixes for contactor interface relay
2025-07-29 Commit to transfer SMT PSU
2025-07-29 Show / hide bits
2025-08-16 Contactor interface cover, bigger PSU container and slow start PSU
2025-08-16 Smaller current sensor for 3oz copper
2025-08-18 Re-orientate pcb dimensions, DIN rail setup
2025-08-18 Adding bento boxes for the pcb
2025-08-18 NFC Logo
2025-08-27 Adding door servo controller
2025-09-04 Progress with work to support door servo
2025-09-06 Progress with the door
2025-09-06 Time to decide what switch to use
2025-09-07 Progress with conical alignment feature
2025-09-07 Commit to modularise door
2025-09-07 Renaming commit
2025-09-08 Mechanism functional
2025-09-08 Pads for TWI, space for 5v signal option
    Copper on the back of relay
2025-09-09 Door handle fixes
2025-09-11 Hex nut size adjustments
2025-09-12 Frameless option for door servo
2025-09-13 Framless fixes and adding lasercut submodule
2025-09-14 Cabinet hinge features
2025-09-14 Assebly with lasercut container
2025-09-16 Updates with perspex cutout and NFC logo
2025-09-20 Holes for window
2025-09-20 Servo Mount in door clip option
2025-09-22 Fighting with FreeCAD
2025-09-29 Freecad project to mill door
2025-10-01 Try again with penisular laser cut module
2025-10-01 Adding lens cap to make white led orange
2025-10-02 General fixes, feet to hold test door
2025-10-03 Update spacer sizes and curving frame-size port
2025-10-04 Move door sensor to the opposite side of servo
2025-11-04 Correct compontent value for Tim
2025-11-04 Measurements for real box
